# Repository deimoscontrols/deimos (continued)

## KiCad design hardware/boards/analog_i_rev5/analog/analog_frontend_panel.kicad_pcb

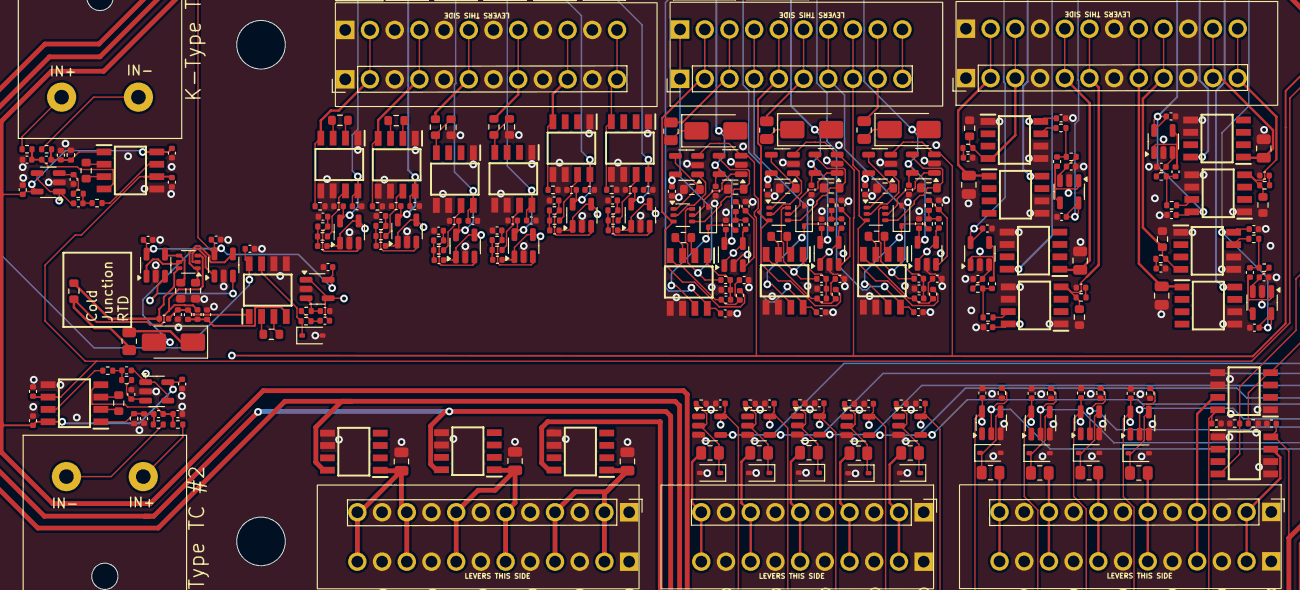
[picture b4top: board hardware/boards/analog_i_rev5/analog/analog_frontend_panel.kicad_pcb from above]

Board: 4 copper layers, 308 parts (0 on the bottom side), 182 nets.

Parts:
C1, C3, C7, C9: 2.2uF; C_0402_1005Metric
C2, C8: 1uF; C_0402_1005Metric
C4, C6, C10, C12, C26, C29, C32, C35, C52, C55, C58, C63, C66, C69, C74, C77, C80, C85, C88, C91, C5003, C8003, C9003, C14003, C15003, C16003, C17003, C18003, C19001, C20003, C21003, C22001, C23001, C24003, C25003, C26001, C27001, C27004, C30003, C31001, C32004, C32005, C33004, C33005, C34002, C37001, C38001, C39001, C39002, C40001, C42001, C44003, C45001: 0.1uF; C_0402_1005Metric
C25, C28, C31, C34, C50, C61, C72, C83: 10nF; C_0402_1005Metric
C49, C51, C60, C62, C71, C73, C82, C84: 1nF; C_0402_1005Metric
C1001, C1002, C1003, C32001, C33001, C34001, C35001: 10uF 50V 0805; C_0805_2012Metric
C5001, C5002, C8001, C8002, C9001, C9002, C14001, C14002, C15001, C15002, C16001, C16002, C17001, C17002, C18001, C18002, C20001, C20002, C21001, C21002, C24001, C24002, C25001, C25002, C30001, C30002, C32002, C32003, C33002, C33003, C44001, C44002: 10nF C0G 5%; C_0402_1005Metric
D7, D8, D9, D10: D_Schottky; D_SMA
D19001, D26001, D27001, D33001, D38001, D39001, D39002, D40001, D42001: BZT52C5V6S; D_SOD-323
D44001, D45001, D46001, D47001: BZT52C3V3; D_SOD-323
H1001, H1002, H1003, H1004: MountingHole_for_10-32; MountingHole_5mm
IC1, IC2, IC5, IC6, IC7, IC8, IC12, IC15, IC18, IC21, IC22001, IC23001, IC27001, IC31001, IC32002, IC34002, IC37001, IC45001: INA826AIDR; SOIC127P600X175-8N
IC13, IC14, IC16, IC17, IC19, IC20, IC22, IC23: TLV333IDBVR; SOT-23-5
IC1001, IC1002, IC1003, IC32001, IC33001, IC34001, IC35001: BD42540FJ-CE2; SOIC127P600X175-8N
J12, J13: AM-K-PCB
J1001, J1004, J1005, J1007: Screw_Terminal_01x12; KF141V-2.54-12P
J1003, J1006: Screw_Terminal_01x10; KF141V-2.54-10P
R1: PTS060301B100RP100; R_0603_1608Metric
R2, R3, R7, R8: 10; R_0402_1005Metric
R4, R9, R19001, R22001, R26001, R27001, R27003, R31002, R32004, R33003, R34001, R37001, R38002, R39002, R39004, R40002, R42002: 1M; R_0402_1005Metric
R6, R11, R40, R49, R58, R67, R23002, R31001, R45003: RNCF0603TKY2K00 2k 0.01% 5ppm/C; R_0603_1608Metric
R22, R24, R26, R28: 200R; R_0402_1005Metric
R23, R25, R27, R29, R32003: RNCF0603TKY75R0 75R 0.01% 5ppm/C; R_0603_1608Metric
R41, R50, R59, R68: 300; R_0805_2012Metric
R42, R43, R51, R52, R60, R61, R69, R70: 10k 1%; C_0402_1005Metric
R44, R47, R53, R56, R62, R65, R71, R74, R23001, R45004: RNCF0603TKW10K0 10k 0.01% 5ppm/C; R_0603_1608Metric
R5001, R5002, R8001, R8002, R9001, R9002: 10k 1%; R_0402_1005Metric
R14001, R14002, R20001, R20002: 100k 1%; R_0402_1005Metric
R15001, R15002, R16001, R16002, R17001, R17002, R18001, R18002, R21001, R21002, R24001, R24002, R25001, R25002, R30001, R30002, R32001, R32002, R33001, R33002, R44001, R44002: 3.3k 1%; R_0402_1005Metric
R19002, R26002, R27002, R33004, R38001, R39001, R39003, R40001, R42001: 49.9; R_0805_2012Metric
U1, U2, U3, U4: NTJD4001NT1G; SOT-363_SC-70-6
U5001, U8001, U9001, U14001, U15001, U16001, U17001, U18001, U20001, U21001, U24001, U25001, U30001, U32001, U33001, U44001: OPA333xxDBV; SOT-23-5
U19001, U26001, U27001, U33002, U38001, U39001, U39002, U40001, U42001: 74LVC1G17; SOT-23-5

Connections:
+1V024: C6.2, C12.2, IC1.6 (REF), IC2.6 (REF)
+2V5: IC13.3 (+IN), IC14.3 (+IN), IC16.3 (+IN), IC17.3 (+IN), IC19.3 (+IN), IC20.3 (+IN), IC22.3 (+IN), IC23.3 (+IN)
+3V3: C4.1, C10.1, C26.2, C29.2, C32.2, C35.2, C55.1, C58.1, C66.1, C69.1, C77.1, C80.1, C88.1, C91.1, C5003.2, C8003.2, C9003.2, C14003.2, C15003.2, C16003.2, C17003.2, C18003.2, C19001.2, C20003.2, C21003.2, C22001.2, C23001.2, C24003.2, C25003.2, C26001.2, C27001.2, C27004.2, C30003.2, C31001.2, C32004.2, C32005.2, C33004.2, C33005.2, C34002.2, C37001.2, C38001.2, C39001.2, C39002.2, C40001.2, C42001.2, C44003.2, C45001.2, D7.2 (A), D8.2 (A), D9.2 (A), D10.2 (A), IC1.8 (+VS), IC2.8 (+VS), IC5.8 (+VS), IC6.8 (+VS), IC7.8 (+VS), IC8.8 (+VS), IC13.5 (V+), IC14.5 (V+), IC16.5 (V+), IC17.5 (V+), IC19.5 (V+), IC20.5 (V+), IC22.5 (V+), IC23.5 (V+), IC22001.8 (+VS), IC23001.8 (+VS), IC27001.8 (+VS), IC31001.8 (+VS), IC32002.8 (+VS), IC34002.8 (+VS), IC37001.8 (+VS), IC45001.8 (+VS), U5001.5 (V+), U8001.5 (V+), U9001.5 (V+), U14001.5 (V+), U15001.5 (V+), U16001.5 (V+), U17001.5 (V+), U18001.5 (V+), U19001.5 (VCC), U20001.5 (V+), U21001.5 (V+), U24001.5 (V+), U25001.5 (V+), U26001.5 (VCC), U27001.5 (VCC), U30001.5 (V+), U32001.5 (V+), U33001.5 (V+), U33002.5 (VCC), U38001.5 (VCC), U39001.5 (VCC), U39002.5 (VCC), U40001.5 (VCC), U42001.5 (VCC), U44001.5 (V+)
+12V: C52.1, C63.1, C74.1, C85.1, IC12.8 (+VS), IC15.8 (+VS), IC18.8 (+VS), IC21.8 (+VS), IC1003.8 (VCC)
+24V: IC1002.8 (VCC), IC32001.8 (VCC), IC33001.8 (VCC), IC34001.8 (VCC), IC35001.8 (VCC)
/4-20mA Frontend1/+24_EXC: C33001.2, IC33001.1 (VO), J1004.8
/4-20mA Frontend1/SIGNAL: IC6.4 (+IN), J1004.9, R24.2, R25.2
/4-20mA Frontend1/sallen_key_3kHz3/VIN: IC6.7 (VOUT), R30001.1
/4-20mA Frontend2/+24_EXC: C34001.2, IC34001.1 (VO), J1004.5
/4-20mA Frontend2/SIGNAL: IC7.4 (+IN), J1004.6, R26.2, R27.2
/4-20mA Frontend2/sallen_key_3kHz3/VIN: IC7.7 (VOUT), R32001.1
/4-20mA Frontend3/+24_EXC: C35001.2, IC35001.1 (VO), J1004.2
/4-20mA Frontend3/SIGNAL: IC8.4 (+IN), J1004.3, R28.2, R29.2
/4-20mA Frontend3/sallen_key_3kHz3/VIN: IC8.7 (VOUT), R33001.1
/4-20mA Frontend/+24_EXC: C32001.2, IC32001.1 (VO), J1004.11
/4-20mA Frontend/SIGNAL: IC5.4 (+IN), J1004.12, R22.2, R23.2
/4-20mA Frontend/sallen_key_3kHz3/VIN: IC5.7 (VOUT), R16001.1
/AIN2: C20002.2, U20001.1, U20001.4 (-)
/AIN3: C16002.2, U16001.1, U16001.4 (-)
/AIN4: C30002.2, U30001.1, U30001.4 (-)
/AIN5: C32003.2, U32001.1, U32001.4 (-)
/AIN6: C33003.2, U33001.1, U33001.4 (-)
/AIN7: C15002.2, U15001.1, U15001.4 (-)
/AIN8: C17002.2, U17001.1, U17001.4 (-)
/AIN9: C18002.2, U18001.1, U18001.4 (-)
/AIN10: C5002.2, U5001.1, U5001.4 (-)
/AIN11: C8002.2, U8001.1, U8001.4 (-)
/AIN12: C21002.2, U21001.1, U21001.4 (-)
/AIN13_DAC0: IC37001.4 (+IN), R37001.1
/AIN14_DAC1: IC34002.4 (+IN), R34001.1
/AIN15: C25002.2, U25001.1, U25001.4 (-)
/AIN16: C44002.2, U44001.1, U44001.4 (-)
/AIN17: C24002.2, U24001.1, U24001.4 (-)
/AIN18: C9002.2, U9001.1, U9001.4 (-)
/AIN19: C14002.2, U14001.1, U14001.4 (-)
/K-Type TC Amp1/Signal+: C7.1, C8.1, IC2.4 (+IN), R7.2
/K-Type TC Amp1/Signal-: C8.2, C9.1, IC2.1 (-IN1), R8.1, R9.1
/K-Type TC Amp1/sallen_key_1kHz/VIN: IC2.7 (VOUT), R8001.1
/K-Type TC Amp/Signal+: C1.1, C2.1, IC1.4 (+IN), R2.2
/K-Type TC Amp/Signal-: C2.2, C3.1, IC1.1 (-IN1), R3.1, R4.1
/K-Type TC Amp/sallen_key_1kHz/VIN: IC1.7 (VOUT), R5001.1
/PWM0: R33003.1, U33002.2
/PWM1: R19001.1, U19001.2
/PWM2: R26001.1, U26001.2
/PWM3: R27001.1, U27001.2
/RTD Amp1/R+: J1006.6, R59.2
/RTD Amp1/R-: J1006.5, R60.2, U3.3 (D2)
/RTD Amp1/W-: J1006.4, R61.2, U3.6 (D1)
/RTD Amp1/rtd_amp_inner/Signal+: C71.2, C72.1, IC18.4 (+IN), R60.1
/RTD Amp1/rtd_amp_inner/Signal-: C72.2, C73.1, IC18.1 (-IN1), R61.1
/RTD Amp1/rtd_amp_inner/Vout: D46001.1 (K), IC18.7 (VOUT), R17001.1
/RTD Amp2/R+: J1006.3, R68.2
/RTD Amp2/R-: J1006.2, R69.2, U4.3 (D2)
/RTD Amp2/W-: J1006.1, R70.2, U4.6 (D1)
/RTD Amp2/rtd_amp_inner/Signal+: C82.2, C83.1, IC21.4 (+IN), R69.1
/RTD Amp2/rtd_amp_inner/Signal-: C83.2, C84.1, IC21.1 (-IN1), R70.1
/RTD Amp2/rtd_amp_inner/Vout: D47001.1 (K), IC21.7 (VOUT), R18001.1
/RTD Amp/R+: J1006.9, R41.2
/RTD Amp/R-: J1006.8, R42.2, U1.3 (D2)
/RTD Amp/W-: J1006.7, R43.2, U1.6 (D1)
/RTD Amp/rtd_amp_inner/Signal+: C49.2, C50.1, IC12.4 (+IN), R42.1
/RTD Amp/rtd_amp_inner/Signal-: C50.2, C51.1, IC12.1 (-IN1), R43.1
/RTD Amp/rtd_amp_inner/Vout: D45001.1 (K), IC12.7 (VOUT), R15001.1
/ain_0-15V_1/VIN: J1005.6, R23001.2
/ain_0-15V_1/sallen_key_3kHz8/VIN: IC23001.7 (VOUT), R24001.1
/ain_0-15V_/VIN: J1005.8, R45004.2
/ain_0-15V_/sallen_key_3kHz8/VIN: IC45001.7 (VOUT), R44001.1
/ain_g1_1/VIN: IC22001.4 (+IN), J1005.10, R22001.1
/ain_g1_1/sallen_key_3kHz7/VIN: IC22001.7 (VOUT), R25001.1
/ain_g1_/VIN: IC27001.4 (+IN), J1005.12, R27003.1
/ain_g1_/sallen_key_3kHz7/VIN: IC27001.7 (VOUT), R21001.1
/ain_g25p7_/VIN: IC31001.4 (+IN), J1005.4, R31002.1
/ain_g25p7_/sallen_key_1kHz2/VIN: IC31001.7 (VOUT), R9001.1
/ain_g666p333_/VIN: IC32002.4 (+IN), J1005.2, R32004.1
/ain_g666p333_/sallen_key_100Hz1/VIN: IC32002.7 (VOUT), R14001.2
/dac_buf1/VOUT: IC34002.7 (VOUT), J1001.4
/dac_buf/VOUT: IC37001.7 (VOUT), J1001.2
/pwm_in_buf1/VIN: J1003.2, R38001.1
/pwm_in_buf2/VIN: J1003.10, R39003.1
/pwm_in_buf3/VIN: J1003.8, R40001.1
/pwm_in_buf4/VIN: J1003.6, R42001.1
/pwm_in_buf/VIN: J1003.4, R39001.1
/pwm_out_buf1/VOUT: J1001.8, R19002.2
/pwm_out_buf2/VOUT: J1001.10, R26002.2
/pwm_out_buf3/VOUT: J1001.12, R27002.2
/pwm_out_buf/VOUT: J1001.6, R33004.2
/rtd_amp_inner1/250uA_SINK_1: R1.1, R52.2, U2.6 (D1)
/rtd_amp_inner1/250uA_SINK_2: R1.2, R50.2, R51.2, U2.3 (D2)
/rtd_amp_inner1/Signal+: C60.2, C61.1, IC15.4 (+IN), R51.1
/rtd_amp_inner1/Signal-: C61.2, C62.1, IC15.1 (-IN1), R52.1
/rtd_amp_inner1/Vout: D44001.1 (K), IC15.7 (VOUT), R20002.2
GND: C1.2, C3.2, C4.2, C6.1, C7.2, C9.2, C10.2, C12.1, C25.2, C26.1, C28.2, C29.1, C31.2, C32.1, C34.2, C35.1, C49.1, C51.2, C52.2, C55.2, C58.2, C60.1, C62.2, C63.2, C66.2, C69.2, C71.1, C73.2, C74.2, C77.2, C80.2, C82.1, C84.2, C85.2, C88.2, C91.2, C1001.1, C1002.1, C1003.1, C5001.1, C5003.1, C8001.1, C8003.1, C9001.1, C9003.1, C14001.1, C14003.1, C15001.1, C15003.1, C16001.1, C16003.1, C17001.1, C17003.1, C18001.1, C18003.1, C19001.1, C20001.1, C20003.1, C21001.1, C21003.1, C22001.1, C23001.1, C24001.1, C24003.1, C25001.1, C25003.1, C26001.1, C27001.1, C27004.1, C30001.1, C30003.1, C31001.1, C32001.1, C32002.1, C32004.1, C32005.1, C33001.1, C33002.1, C33004.1, C33005.1, C34001.1, C34002.1, C35001.1, C37001.1, C38001.1, C39001.1, C39002.1, C40001.1, C42001.1, C44001.1, C44003.1, C45001.1, D19001.2 (A), D26001.2 (A), D27001.2 (A), D33001.2 (A), D38001.2 (A), D39001.2 (A), D39002.2 (A), D40001.2 (A), D42001.2 (A), D44001.2 (A), D45001.2 (A), D46001.2 (A), D47001.2 (A), IC1.5 (-VS), IC2.5 (-VS), IC5.1 (-IN1), IC5.5 (-VS), IC5.6 (REF), IC6.1 (-IN1), IC6.5 (-VS), IC6.6 (REF), IC7.1 (-IN1), IC7.5 (-VS), IC7.6 (REF), IC8.1 (-IN1), IC8.5 (-VS), IC8.6 (REF), IC12.5 (-VS), IC12.6 (REF), IC13.2 (V-), IC14.2 (V-), IC15.5 (-VS), IC15.6 (REF), IC16.2 (V-), IC17.2 (V-), IC18.5 (-VS), IC18.6 (REF), IC19.2 (V-), IC20.2 (V-), IC21.5 (-VS), IC21.6 (REF), IC22.2 (V-), IC23.2 (V-), IC1001.5 (ADJ_/_EN), IC1001.6 (GND), IC1002.5 (ADJ_/_EN), IC1002.6 (GND), IC1003.5 (ADJ_/_EN), IC1003.6 (GND), IC22001.1 (-IN1), IC22001.5 (-VS), IC22001.6 (REF), IC23001.1 (-IN1), IC23001.5 (-VS), IC23001.6 (REF), IC27001.1 (-IN1), IC27001.5 (-VS), IC27001.6 (REF), IC31001.1 (-IN1), IC31001.5 (-VS), IC31001.6 (REF), IC32001.5 (ADJ_/_EN), IC32001.6 (GND), IC32002.1 (-IN1), IC32002.5 (-VS), IC32002.6 (REF), IC33001.5 (ADJ_/_EN), IC33001.6 (GND), IC34001.5 (ADJ_/_EN), IC34001.6 (GND), IC34002.1 (-IN1), IC34002.5 (-VS), IC34002.6 (REF), IC35001.5 (ADJ_/_EN), IC35001.6 (GND), IC37001.1 (-IN1), IC37001.5 (-VS), IC37001.6 (REF), IC45001.1 (-IN1), IC45001.5 (-VS), IC45001.6 (REF), J1001.1, J1001.3, J1001.5, J1001.7, J1001.9, J1001.11, J1003.1, J1003.3, J1003.5, J1003.7, J1003.9, J1004.1, J1004.4, J1004.7, J1004.10, J1005.1, J1005.3, J1005.5, J1005.7, J1005.9, J1005.11, J1007.1, J1007.3, J1007.5, J1007.7, J1007.9, J1007.11, R4.2, R9.2, R23.1, R25.1, R27.1, R29.1, R44.2, R47.2, R53.2, R56.2, R62.2, R65.2, R71.2, R74.2, R19001.2, R22001.2, R23002.2, R26001.2, R27001.2, R27003.2, R31002.2, R32004.2, R33003.2, R34001.2, R37001.2, R38002.2, R39002.2, R39004.2, R40002.2, R42002.2, R45003.2, U5001.2 (V-), U8001.2 (V-), U9001.2 (V-), U14001.2 (V-), U15001.2 (V-), U16001.2 (V-), U17001.2 (V-), U18001.2 (V-), U19001.3 (GND), U20001.2 (V-), U21001.2 (V-), U24001.2 (V-), U25001.2 (V-), U26001.3 (GND), U27001.3 (GND), U30001.2 (V-), U32001.2 (V-), U33001.2 (V-), U33002.3 (GND), U38001.3 (GND), U39001.3 (GND), U39002.3 (GND), U40001.3 (GND), U42001.3 (GND), U44001.2 (V-)
unnamed: C25.1, R22.1
unnamed: C28.1, R24.1
unnamed: C31.1, R26.1
unnamed: C34.1, R28.1
unnamed: C5002.1, R5001.2, R5002.1
unnamed: C8002.1, R8001.2, R8002.1
unnamed: C9002.1, R9001.2, R9002.1
unnamed: C14002.1, R14001.1, R14002.2
unnamed: C15002.1, R15001.2, R15002.1
unnamed: C16002.1, R16001.2, R16002.1
unnamed: C17002.1, R17001.2, R17002.1
unnamed: C18002.1, R18001.2, R18002.1
unnamed: C20002.1, R20001.2, R20002.1
unnamed: C21002.1, R21001.2, R21002.1
unnamed: C24002.1, R24001.2, R24002.1
unnamed: C25002.1, R25001.2, R25002.1
unnamed: C30002.1, R30001.2, R30002.1
unnamed: C32003.1, R32001.2, R32002.1
unnamed: C33003.1, R33001.2, R33002.1
unnamed: C44002.1, R44001.2, R44002.1
unnamed: D7.1 (K), R41.1
unnamed: D8.1 (K), R50.1
unnamed: D9.1 (K), R59.1
unnamed: D10.1 (K), R68.1
unnamed: D19001.1 (K), R19002.1, U19001.4
unnamed: D26001.1 (K), R26002.1, U26001.4
unnamed: D27001.1 (K), R27002.1, U27001.4
unnamed: D33001.1 (K), R33004.1, U33002.4
unnamed: D38001.1 (K), R38001.2, R38002.1, U38001.2
unnamed: D39001.1 (K), R39001.2, R39002.1, U39001.2
unnamed: D39002.1 (K), R39003.2, R39004.1, U39002.2
unnamed: D40001.1 (K), R40001.2, R40002.1, U40001.2
unnamed: D42001.1 (K), R42001.2, R42002.1, U42001.2
unnamed: IC1.2 (RG_1), R6.1
unnamed: IC1.3 (RG_2), R6.2
unnamed: IC2.2 (RG_1), R11.1
unnamed: IC2.3 (RG_2), R11.2
unnamed: IC12.2 (RG_1), R40.1
unnamed: IC12.3 (RG_2), R40.2
unnamed: IC13.4 (-IN), R44.1, U1.1 (S1)
unnamed: IC13.1 (OUT), U1.2 (G1)
unnamed: IC14.4 (-IN), R47.1, U1.4 (S2)
unnamed: IC14.1 (OUT), U1.5 (G2)
unnamed: IC15.2 (RG_1), R49.1
unnamed: IC15.3 (RG_2), R49.2
unnamed: IC16.4 (-IN), R53.1, U2.1 (S1)
unnamed: IC16.1 (OUT), U2.2 (G1)
unnamed: IC17.4 (-IN), R56.1, U2.4 (S2)
unnamed: IC17.1 (OUT), U2.5 (G2)
unnamed: IC18.2 (RG_1), R58.1
unnamed: IC18.3 (RG_2), R58.2
unnamed: IC19.4 (-IN), R62.1, U3.1 (S1)
unnamed: IC19.1 (OUT), U3.2 (G1)
unnamed: IC20.4 (-IN), R65.1, U3.4 (S2)
unnamed: IC20.1 (OUT), U3.5 (G2)
unnamed: IC21.2 (RG_1), R67.1
unnamed: IC21.3 (RG_2), R67.2
unnamed: IC22.4 (-IN), R71.1, U4.1 (S1)
unnamed: IC22.1 (OUT), U4.2 (G1)
unnamed: IC23.4 (-IN), R74.1, U4.4 (S2)
unnamed: IC23.1 (OUT), U4.5 (G2)
unnamed: C1001.2, IC1001.1 (VO), J1007.2, J1007.4
unnamed: C1002.2, IC1002.1 (VO), J1007.10, J1007.12
unnamed: C1003.2, IC1003.1 (VO), J1007.6, J1007.8
unnamed: IC23001.4 (+IN), R23001.1, R23002.1
unnamed: IC31001.2 (RG_1), R31001.1
unnamed: IC31001.3 (RG_2), R31001.2
unnamed: IC32002.2 (RG_1), R32003.1
unnamed: IC32002.3 (RG_2), R32003.2
unnamed: IC45001.4 (+IN), R45003.1, R45004.1
unnamed: J12.1, R3.2
unnamed: J12.2, R2.1
unnamed: J13.1, R8.2
unnamed: J13.2, R7.1
unnamed: C5001.2, R5002.2, U5001.3 (+)
unnamed: C8001.2, R8002.2, U8001.3 (+)
unnamed: C9001.2, R9002.2, U9001.3 (+)
unnamed: C14001.2, R14002.1, U14001.3 (+)
unnamed: C15001.2, R15002.2, U15001.3 (+)
unnamed: C16001.2, R16002.2, U16001.3 (+)
unnamed: C17001.2, R17002.2, U17001.3 (+)
unnamed: C18001.2, R18002.2, U18001.3 (+)
unnamed: C20001.2, R20001.1, U20001.3 (+)
unnamed: C21001.2, R21002.2, U21001.3 (+)
unnamed: C24001.2, R24002.2, U24001.3 (+)
unnamed: C25001.2, R25002.2, U25001.3 (+)
unnamed: C30001.2, R30002.2, U30001.3 (+)
unnamed: C32002.2, R32002.2, U32001.3 (+)
unnamed: C33002.2, R33002.2, U33001.3 (+)
unnamed: C44001.2, R44002.2, U44001.3 (+)

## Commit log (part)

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2026-05-03 wip to update enclosure labels
2026-05-03 finish first pass of side labels
2026-05-03 enlarge eth cutout
2026-05-03 add logo
2026-05-03 set finish
2026-05-03 finish materials
2026-05-10 add svg converter script and converted svgs
2026-05-16 Rev7 enclosure graphics (#47)
    * Slightly widen eth port cutout
    * Small shift to TC port cutout origins
    * Add graphics to front and back panels
2026-05-23 as-quoted enclosure STEP file
2026-05-24 remove unused imports. update version and changelog.
2026-05-24 note numerics updates
2026-05-24 as-quoted enclosure cad
2026-05-24 resolve new clippy lints
2026-05-24 update changelog
2026-05-24 add notes about why Normed trait is imported
2026-05-24 update socket2 version
2026-05-24 update deimos_console dep versions
2026-05-24 Updates for 0.16.2 release (#49)
2026-05-31 light mode toggle
2026-06-02 record flashing rev7 sn2
2026-06-02 references for delta operator
2026-06-09 update multidaq example
2026-06-09 add embedded-alloc and flip-link
2026-06-09 demo live filter construction
2026-06-09 add DeltaSOS::set_steady_state. use DeltaSOS filters in rev7 firmware.
2026-06-09 add MedianSort in deimos_numerics
2026-06-11 add filter construction shortcuts. use delta-SOS filter for application side filtering.
2026-06-11 move rev7 filter construction to deimos_shared
2026-06-11 pull constants out to shared module and reuse
2026-06-11 port website
2026-06-11 update website deployment
2026-06-11 migration plan
2026-06-11 add analog filter transfer functions
2026-06-11 frequencies in hz
2026-06-12 better bode plots
2026-06-12 better annotations
2026-06-12 adjustable plots
2026-06-12 plot margins
2026-06-12 plot title
2026-06-12 fonts
2026-06-13 more changelog
2026-06-13 major version roll
2026-06-13 update versions
2026-06-13 reject python -O
2026-06-13 add better path detection for chromium
2026-06-13 add mark at nyquist of reporting rate
2026-06-13 use deimos_numerics median filter for timing controller
2026-06-13 ruff fmt
2026-06-13 exclude coverage of import trap
2026-06-13 Analytic filter construction (#51)
    ## 2026-06-08 0.17.0
    This update moves the rev7 firmware's filter construction and runtime
    from `flaw` to `deimos_numerics`, and from interpolated to analytic
    construction. The filter construction pipeline is moved to deimos_shared
    and adds access to filter transfer functions on the application side
    that exactly match the ones used by the firmware, along with an example
2026-06-14 calibration workflow for 4-20mA
2026-06-14 first cut of RTD calibration procedure
2026-06-14 continue building up RTD cal procedure
2026-06-14 box plots
2026-06-14 box plots with std dev
2026-06-15 generate both dark and light plots. add calibrator uncertainty spec to plot.
2026-06-15 WIP to add thermocouple calibration procedure
2026-06-15 remove initial calc eval so that filters initialize properly
2026-06-15 changelog
2026-06-16 temporary thermocouple fix with inverse table
2026-06-16 update to use polynomials for thermocouples instead of tables
2026-06-16 widen band for tc
2026-06-16 calibrate voltage under thermocouple channels
2026-06-16 simplify TC procedure
2026-06-16 better TC postprocessing
2026-06-16 better plots
2026-06-16 clean up new RTD functions
2026-06-17 first cut of voltage calibration procedure
2026-06-17 rev 7.0.1 hardware with fixed shunt, increased LED power, and added cutout for light pipes
2026-06-18 show fluke voltage range
2026-06-18 do not fit cals for voltages if they fall entirely inside calibrator uncertainty
2026-06-18 update dep versions
2026-06-18 update license rollup
2026-06-18 add calibration records in website. move cal procedure to peripheral module.
2026-06-18 continue migrating cal procedure
2026-06-20 wip to update peripheral trait to accommodate cals
2026-06-20 continue updating trait for cals
2026-06-20 update existing peripherals and controller for new API
2026-06-21 update PluginFn signature
2026-06-21 continuing wip to build up calibration records
2026-06-21 impl default
2026-06-21 add generation of cal record to procedure
2026-06-21 process sn2 cal data and produce cal.json
2026-06-21 add calibration querying and caching
2026-06-21 wire calibrations into controller
2026-06-21 wire calibrations into rev7 standard calcs and update calibrations to apply to sensed voltage. add calcs to expose sensed voltages.
2026-06-21 first cut of replay
2026-06-21 update calibration procedure to nominally go through the replay path to be robust to reprocessing
2026-06-21 add flag for skipping calibrations
2026-06-21 take new calibration data and reprocess
2026-06-22 rename cals folder to records
2026-06-22 reprocess and add records to nav
2026-06-22 get nav working
2026-06-22 compress raw cal data
2026-06-22 remove vestigial error_samples csv
2026-06-22 plot formatting
2026-06-23 add plots of lookups
2026-06-23 sensitivity plots
2026-06-23 update bode plot examples
2026-06-25 rev7 SN1 calibrations
2026-06-25 add local cal store for examples
2026-06-27 improve plots
2026-06-27 docs for fluke 707
2026-06-27 add va720 docs
2026-06-27 va710 docs
2026-06-27 record calibrators on existing runs
2026-06-27 wip to update website and readme
2026-06-27 wip to update website
2026-06-28 prevent bode plots from folding
2026-06-28 improve spec sheet
2026-06-28 wip to update landing page
2026-06-28 text color
2026-06-28 wip to improve landing page
2026-06-28 fold email signup on top
2026-06-28 continuing wip on landing page
2026-06-28 update social links
2026-06-28 continuing wip to update landing page
2026-06-28 clean up plot frames
2026-06-28 zoomable
2026-06-28 update number of outputs
2026-06-28 wip to update python api docs
2026-06-28 update python api docs
2026-06-28 diagram style
2026-06-28 rustdoc theme
2026-06-28 beta-testing splash
2026-06-28 mention open source earlier
2026-06-28 Resolve rustdoc lints
2026-06-28 test existing calibrations
2026-06-29 remove stub for unusable constructor
2026-06-29 format
2026-06-29 Implement calibration (#52)
    ## 2026-06-28 0.18.0
    This update adds calibration procedures for the Rev7 and wires
    calibration handling into the controller, calc orchestrator,
    and peripheral trait. It also adds and ultra-lightweight, open-access
    calibration database as part of the static site, populated with the
    first set of calibrations.
2026-06-30 add system diagram
2026-06-30 update landing page
2026-06-30 Update website system diagram (#53)
